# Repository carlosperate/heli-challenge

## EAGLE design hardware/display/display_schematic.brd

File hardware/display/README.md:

Display Sub-System Eagle files
==============

This directory contains the eagle files for the display subsystem.

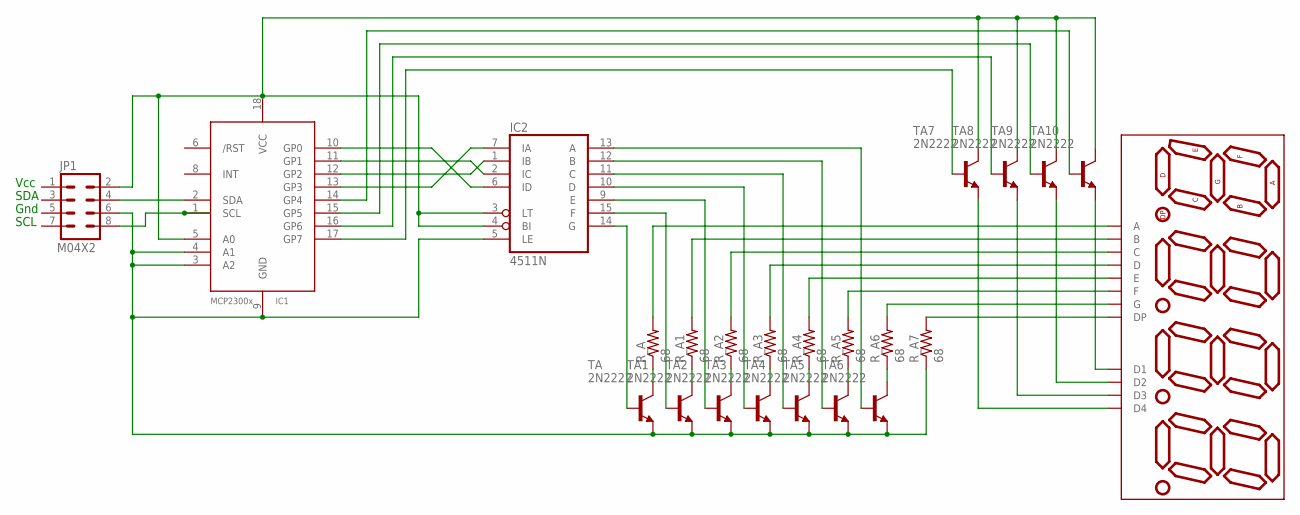
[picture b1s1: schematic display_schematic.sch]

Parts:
DISPLAY7S4D1: 7SEG-4DIG-NEW
IC1: MCP2300X/P; DIL18
IC2: 4511N; DIL16
JP1: M04X2; 2X4
R_A, R_A1, R_A2, R_A3, R_A4, R_A5, R_A6, R_A7: 68; AXIAL-0.3
TA, TA1, TA2, TA3, TA4, TA5, TA6, TA7, TA8, TA9, TA10: 2N2222; TO92-EBC-OVAL

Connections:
unnamed: IC1.5 (A0), IC1.18 (VCC), IC2.3 (LT), IC2.4 (BI), JP1.2, TA7.C, TA8.C, TA9.C, TA10.C
unnamed: IC1.3 (A2), IC1.4 (A1), IC1.9 (GND), IC2.5 (LE), JP1.6, R_A7.P$1 (1), TA.E, TA1.E, TA2.E, TA3.E, TA4.E, TA5.E, TA6.E
unnamed: IC1.2 (SDA), JP1.4
unnamed: IC1.1 (SCL), JP1.8
unnamed: IC2.14 (G), TA.B
unnamed: DISPLAY7S4D1.11 (A), R_A.P$2 (2)
unnamed: IC1.13 (GP3), IC2.7 (IA)
unnamed: IC1.11 (GP1), IC2.2 (IC)
unnamed: IC1.12 (GP2), IC2.1 (IB)
unnamed: IC1.10 (GP0), IC2.6 (ID)
unnamed: IC1.14 (GP4), TA10.B
unnamed: IC1.15 (GP5), TA9.B
unnamed: IC1.16 (GP6), TA8.B
unnamed: IC2.15 (F), TA1.B
unnamed: DISPLAY7S4D1.7 (B), R_A1.P$2 (2)
unnamed: IC2.9 (E), TA2.B
unnamed: DISPLAY7S4D1.4 (C), R_A2.P$2 (2)
unnamed: DISPLAY7S4D1.2 (D), R_A3.P$2 (2)
unnamed: IC1.17 (GP7), TA7.B
unnamed: DISPLAY7S4D1.1 (E), R_A4.P$2 (2)
unnamed: DISPLAY7S4D1.10 (F), R_A5.P$2 (2)
unnamed: DISPLAY7S4D1.5 (G), R_A6.P$2 (2)
unnamed: IC2.10 (D), TA3.B
unnamed: IC2.11 (C), TA4.B
unnamed: IC2.12 (B), TA5.B
unnamed: IC2.13 (A), TA6.B
unnamed: DISPLAY7S4D1.3 (DP), R_A7.P$2 (2)
unnamed: DISPLAY7S4D1.6 (D4), TA7.E
unnamed: DISPLAY7S4D1.8 (D3), TA8.E
unnamed: DISPLAY7S4D1.9 (D2), TA9.E
unnamed: DISPLAY7S4D1.12 (D1), TA10.E
TR_A: R_A.P$1 (1), TA.C
TR_A1: R_A1.P$1 (1), TA1.C
TR_A2: R_A2.P$1 (1), TA2.C
TR_A3: R_A3.P$1 (1), TA3.C
TR_A4: R_A4.P$1 (1), TA4.C
TR_A5: R_A5.P$1 (1), TA5.C
TR_A6: R_A6.P$1 (1), TA6.C
VDD: IC2.16 (VDD)
VSS: IC2.8 (VSS)

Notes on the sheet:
Vcc
SCL
SDA
Gnd

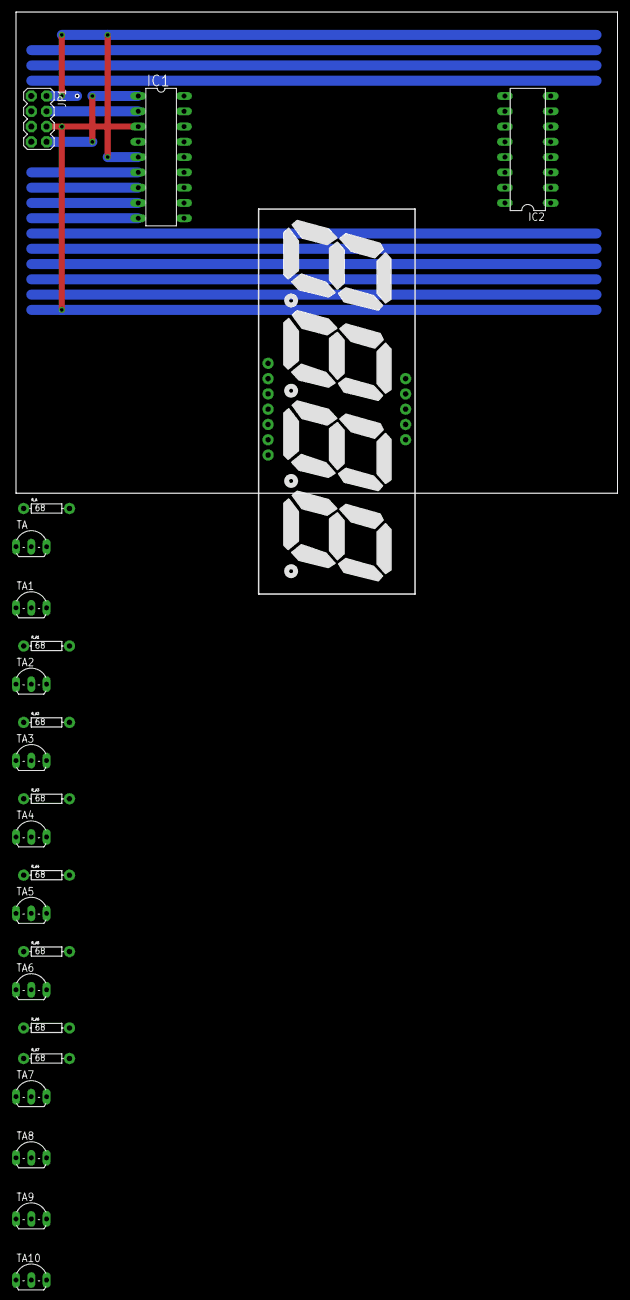
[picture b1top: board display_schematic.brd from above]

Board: 2 copper layers, 100.0 x 80.0 mm, 23 parts (0 on the bottom side), 38 nets.

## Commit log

2013-04-19 Initial commit (moving from SVN private repo to public GitHub) with the current state of the software project.
2013-04-22 Rename of the "swprojectfolder" to just "software". Adding the "hardware folder" with a subfolder+readme for each subsystem. Adding the current version of the eagle files for the display board.
2013-04-22 gitignore Adding extra file extensions and directories to the gitignore file.
2013-04-22 Schematics Updating display schematic and adding schematics for ledarrows and servos. Also adding image exports for simplified illustration.
2013-04-22 gitignore Updating the gitignore file with the latest changes from the folder structure.
2013-04-23 Updating schematics of servos and ledarrows to include the db15 connector used to interface outside of the electronics enclosure.
2013-04-29 Adding the time control module to the software.
2013-04-29 Updating the comments for completeness and to adhere to the Doxygen format.
2013-04-30 Finishing up the display control module. Still needs testing on the hardware.
2013-05-01 ADC->servo and start on joystick buttons
2013-05-01 joystick buttons start
    also removed joystickservo.h from includes - should be moved - cleaned
    up? can you reject those changes?..i dont understand how github works
2013-05-02 Schematics updates: Adding a shield schematic file for the microcontroller board header connector and power breakdown. Adding page border to existing schematics. Adding a few component values. Updati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
2013-05-02 Code clean up and scheduler updates.
2013-05-02 Updating the gitignore to leave eclipse/codewarrior metadata out.
2013-05-02 restored schematics updates lost with merge.
2013-05-02 Removing the need to send unsigned characters to the uart module and removes the need to
2013-05-02 Restoring loses from merging
2013-05-02 Implementing the machine state. Also adding a dummy file to eliminate stupid warning from CodeWarrior.
2013-05-04 build tested on Friday
2013-05-06 Updating the schematics to include A5 frames and complete some component values. Also adding the arduino shield symbol to the shield schematic.
2013-05-07 Updated display code to latch a single digit per task iteration. I2C pinout changed to P8 and P9. Commenting out display code that causes hang ups if I2C bus not connected. Switch machine state now c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
2013-05-08 FIxing processorexpert.pe
2013-05-09 Update shield schematic: Only uses a single 3.3V regulator. Added the I2C connector and pull ups. Added a note to the SDA UART RX (uC TX) pin used for debugging.
2013-05-13 Capacitive touch input library added. Further configuration and testing still required.
2013-05-20 incl early calib
2013-05-21 Commit calibrate
2013-05-21 PinOut changes in processor expert: Changed the servo, LEDS, and joystic inputs. Removed blue LED (from RGB) component as it will be used for servo. Code for capacitive input updated in working order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
2013-05-21 Uncommented library call removed due to code merging. All should be fixed now.
2013-05-22 Joystick inputs: activated the internal pull up for the joystick buttons inputs. Renamed joystick4 to joystick 1 to correlate with the software. streamlined the debug to terminal information to fit m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
2013-05-22 Joystick and servo data transfer: Added calibration local globals in joysticservo. Refactor the js_AdcToUs function to converter the ADC readout to a servo time relative to the joystick calibration. 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
2013-05-23 Deactivating the NMI function from the uC in order to use PTA4 for PWM output.
2013-05-24 Increasing speed of uC. Divided the ADC to servo function into X and Y servos. Added the calibration code to the state machine calibration state. Changed the I2C speed to ~350KHz. Display refreshed a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
2013-05-24 Dividing joystickservo module and merging all joystick related into jostick.h/.c/ modify the debug function print information more effectively. updated the scheduler. calibration mode implemented, st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
2013-05-24 adding led blocks module and test in application.c
2013-05-25 Adding box button in processor expert.
2013-05-26 debug functions added to debug.h/.c
2013-05-26 calibration limits implemented in joystick get X and Y functions.
2013-05-27 Fixed a couple of bugs with the calibrated X and Y joystick functions. Added the box button as part of the game select.
2013-05-27 updating resistor values in schematics
2013-05-28 Increase time accuracy of task tick: Changed from 100Hz RTOS tick to 500Hz. Changed the I2C speed to a round 300KHz speed.
2013-05-28 Clean up of processor expert components
2013-05-28 Update of time module and "play mode" state. Changed the task for the display to run at 500Hz. Updated the display module to flash all digits at each task iteration.
2013-06-05 Adding simple difficulty levels increased with time.
2013-06-14 Processor Expert components: I2C clocking changes for stability Both PWM now start at medium point 1500usec LED Arrows now in correct IOs to correlate with position Playing with TSS for capacitive se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
2013-06-14 Correcting issue with data not updated in the Time Module.
2013-06-14 Removing compiler warnings.
2013-06-14 Updating events and other files dependent on Processor Expert.
2013-06-14 Multiple Updates: Y Axis inverted for correct control. Scheduler updated to change task frequency from 20hz to 40hz Display module task runs at 500HZ (as before) but now it turns on a segment for eac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
2013-06-14 Removing dead code from joystick.c.
2013-06-14 Capacitive sensor configured to detect human touch in the activity platform. Changes to Processor Expert component and related files.
2013-06-17 TSS new settings for touch detection in the outer ring of the platform. However code in interrupt has been commented out as function only work with human touch and not the rubber balls.
2013-06-17 Reverted Y axis joystick movement. Improved gameplay with difficulty levels. Removing unnecessary files from old code.
2013-06-18 Heli-Challenge binary version 0.1 Attended the science day. All functioning except for capacitive sensor.
2013-06-26 Refactoring the joysticservo module into a servocontrol and individual gameplay modules.
2013-07-12 gameplay bug fix and modification of difficulty levels timings.

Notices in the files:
parts and their libraries:
SparkFun-Connectors: Licensing: CC v3.0 Share-Alike You are welcome to use this library for commercial purposes.
